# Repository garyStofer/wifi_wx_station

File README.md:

# wifi_wx_station
This project is for a full featured, self contained weather station that connects via WiFi to home network and uploads periodic readings
to various cloud based weather data ingestion service, such as Weather Underground, CWOP, WOW, etc.

The hardware is based on a Microchip controller with an attached Microchip WiFi module. 
The various sensors arepart of the project with the air data sensors (baro/temp/hyg) based onn i2C devices. 
The wind sensord are of unique solid state design ( optical, magnetic) and proide a high degree of precision, fidelity and reliability.

More information at http://wws.us.to

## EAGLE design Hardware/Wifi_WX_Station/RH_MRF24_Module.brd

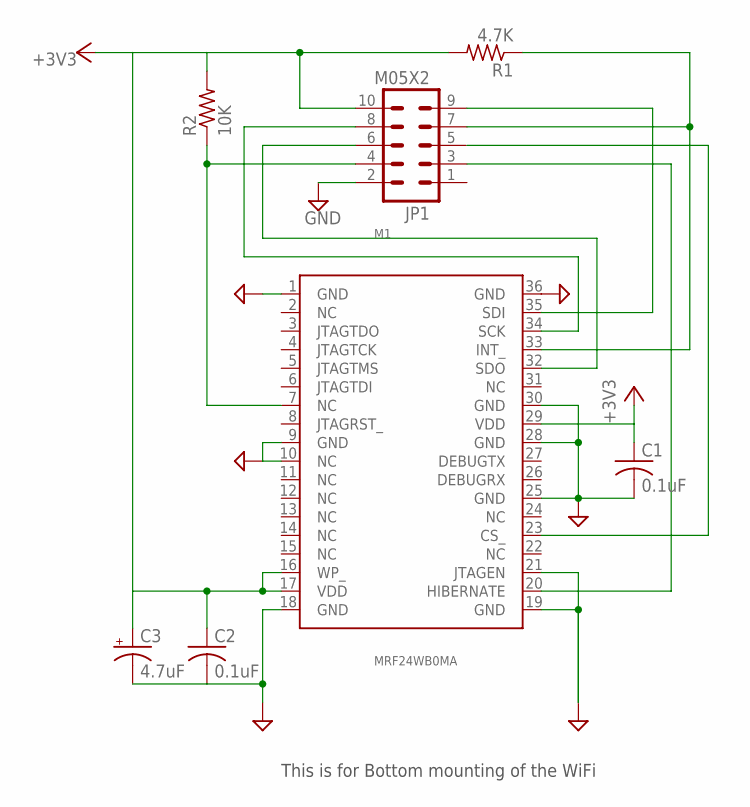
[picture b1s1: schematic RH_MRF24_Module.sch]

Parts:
C1, C2: 0.1uF; C0805
C3: 4.7uF; R/2012-12R
JP1: M05X2; 2X5-RA-HEADER
M1: MRF24WB0MA; MRF24W
R1: 4.7K; R0603
R2: 10K; R0603

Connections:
+3V3: C1.1, C2.1, C3.+, JP1.10, M1.16 (WP_), M1.17 (VDD), M1.29 (VDD), R1.2, R2.2
CS_: JP1.5, M1.23 (CS_)
GND: C1.2, C2.2, C3.-, JP1.2, M1.1 (GND), M1.9 (GND), M1.10 (NC), M1.18 (GND), M1.19 (GND), M1.21 (JTAGEN), M1.25 (GND), M1.28 (GND), M1.30 (GND), M1.36 (GND)
HIBER: JP1.3, M1.20 (HIBERNATE)
INT_: JP1.7, M1.33 (INT_), R1.1
RESET_: JP1.4, M1.7 (NC), R2.1
SCK: JP1.8, M1.34 (SCK)
SDI: JP1.9, M1.35 (SDI)
SDO: JP1.6, M1.32 (SDO)

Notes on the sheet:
This is for Bottom mounting of the WiFi

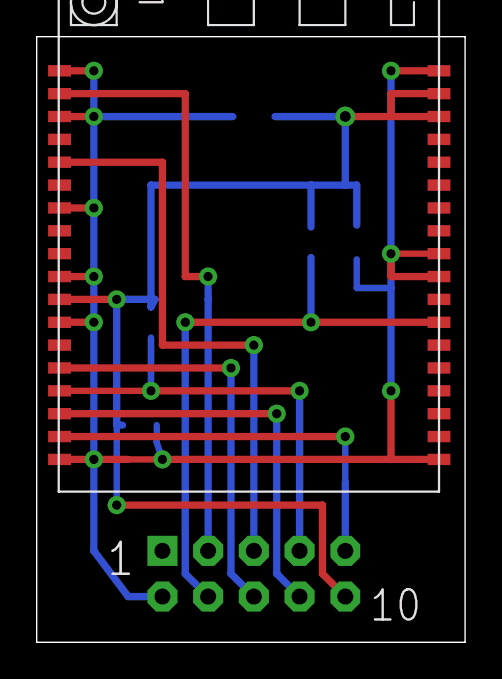
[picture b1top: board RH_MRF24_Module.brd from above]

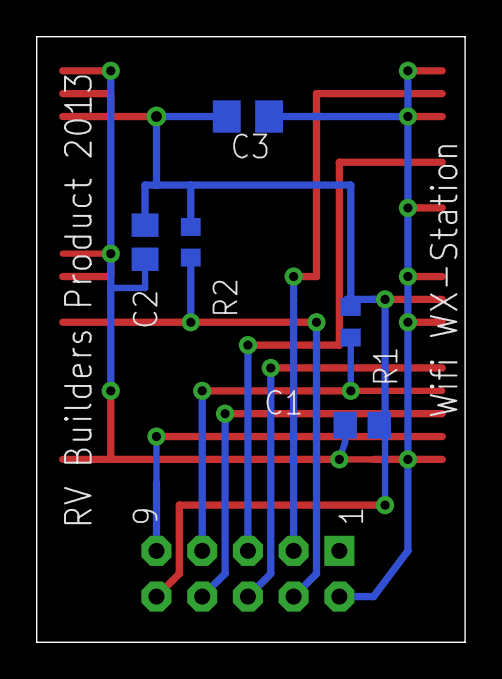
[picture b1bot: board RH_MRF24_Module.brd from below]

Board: 2 copper layers, 23.8 x 33.6 mm, 7 parts (6 on the bottom side), 9 nets.

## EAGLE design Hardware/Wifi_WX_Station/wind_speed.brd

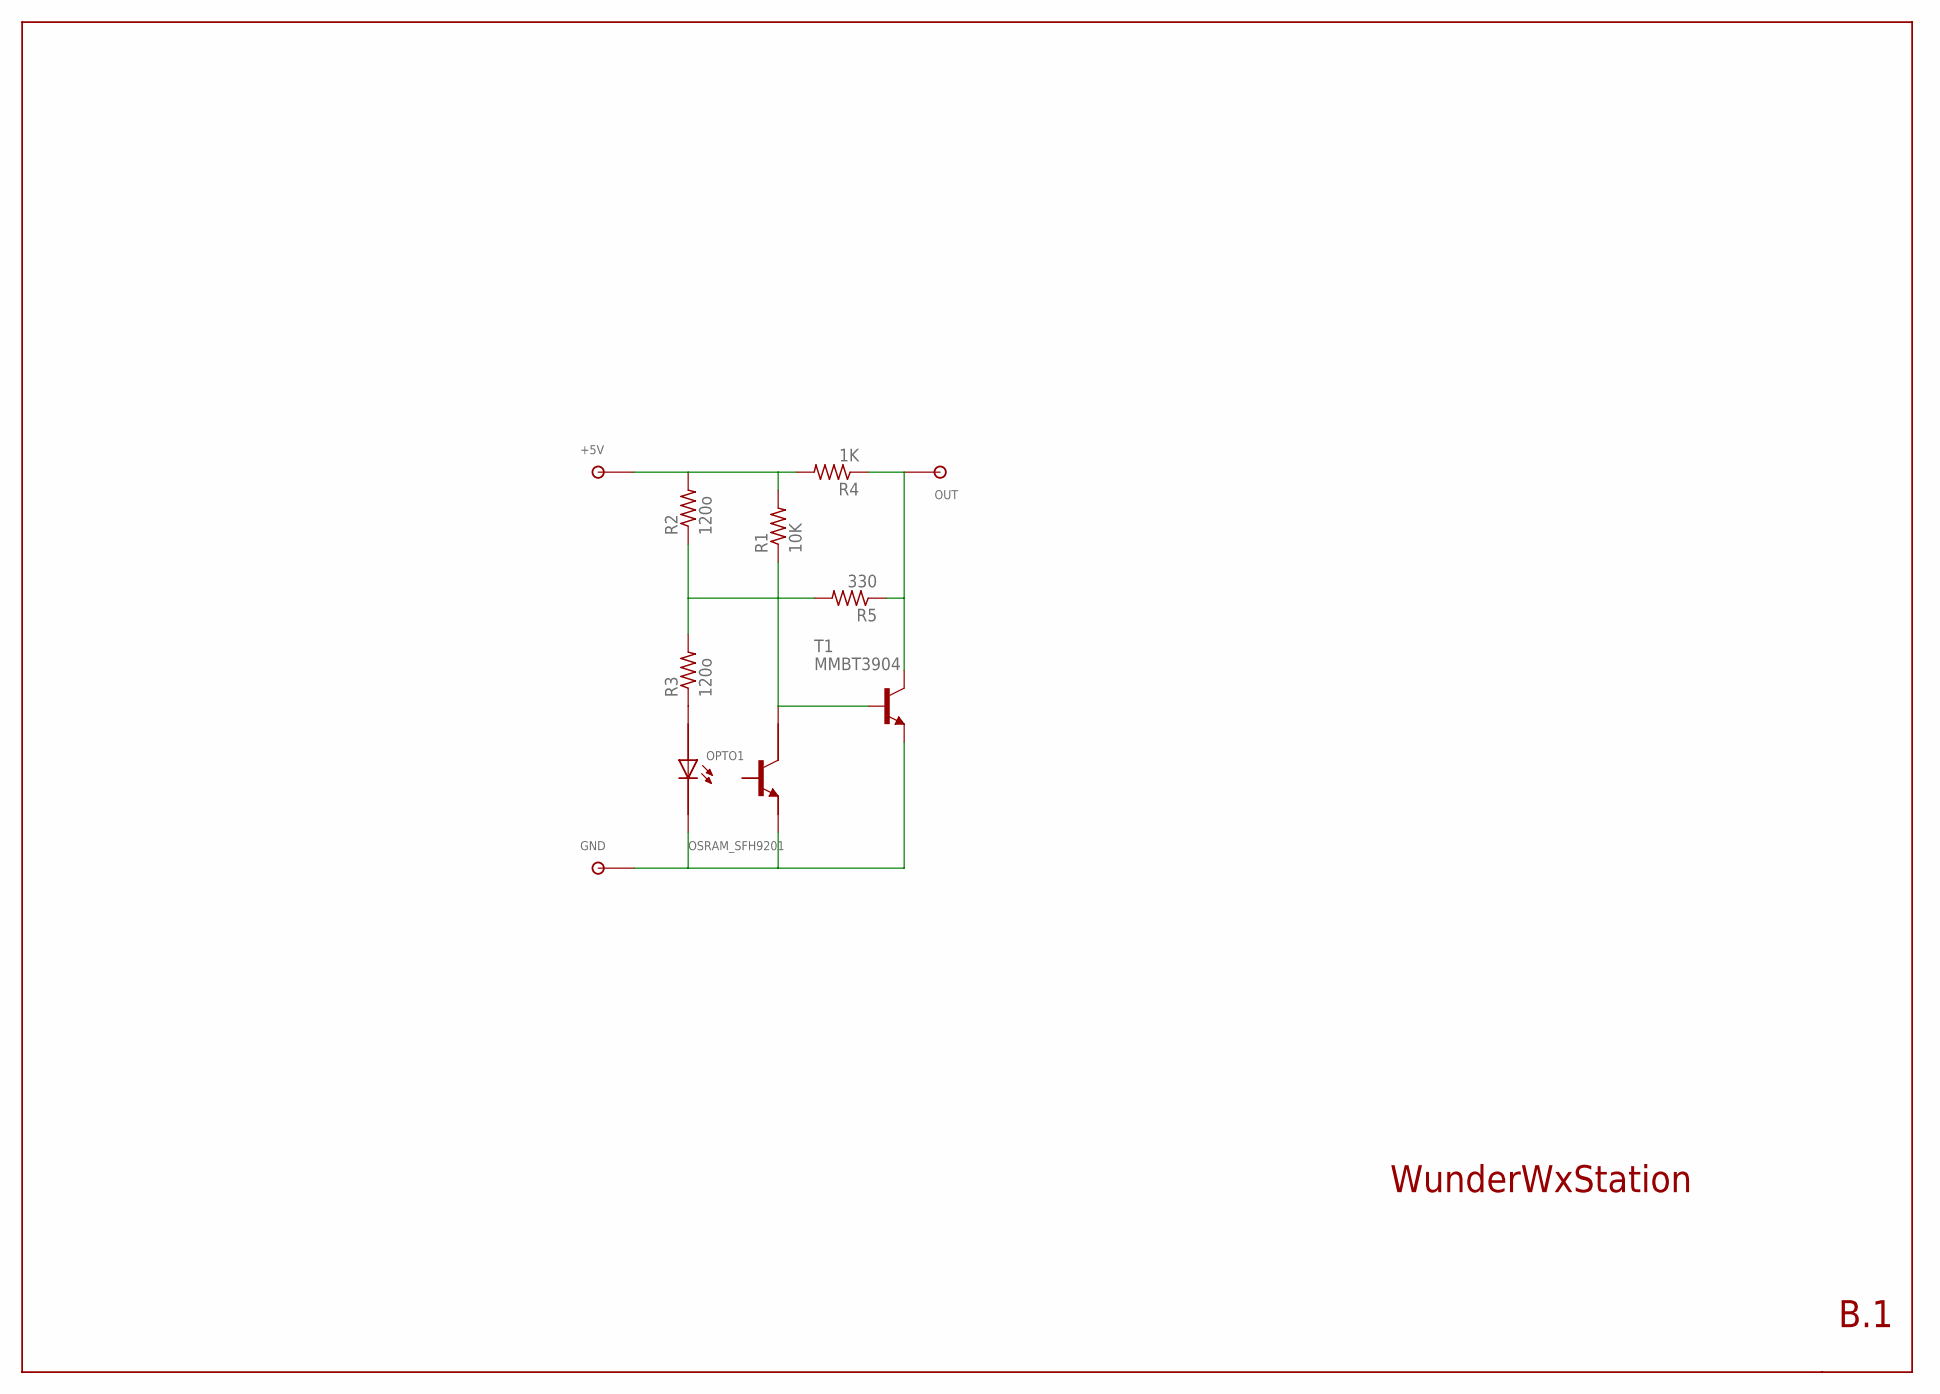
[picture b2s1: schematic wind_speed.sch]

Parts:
+5V: TPSOL; TP_SOL
GND: TPSOL; TP_SOL
OPTO1: OSRAM_SFH9201; OSRAM-6
OUT: TPSOL; TP_SOL
R1: 10K; R0603
R2, R3: 120o; R0603
R4: 1K; R0603
R5: 330; R0603
T1: MMBT3904; SOT23

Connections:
unnamed: OPTO1.P$4 (C), R1.1, T1.1 (B)
unnamed: GND.P$1, OPTO1.P$3 (E), OPTO1.P$6 (CATH), T1.2 (E)
unnamed: +5V.P$1, R1.2, R2.2, R4.2
unnamed: OUT.P$1, R4.1, R5.1, T1.3 (C)
unnamed: OPTO1.P$1 (AN), R3.1
unnamed: R2.1, R3.2, R5.2

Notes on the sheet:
WunderWxStation
B.1

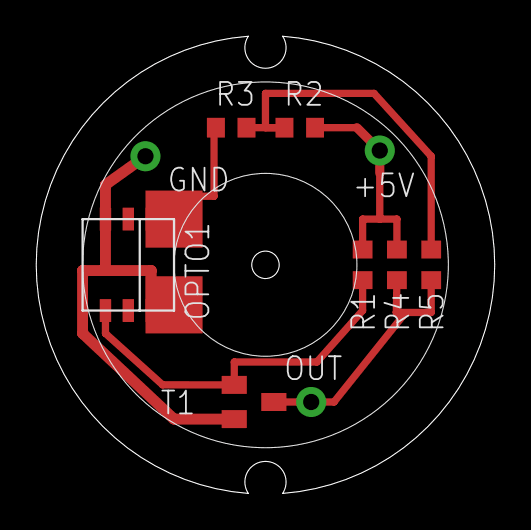
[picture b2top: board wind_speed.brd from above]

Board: 2 copper layers, 25.5 x 25.4 mm, 10 parts (0 on the bottom side), 6 nets.

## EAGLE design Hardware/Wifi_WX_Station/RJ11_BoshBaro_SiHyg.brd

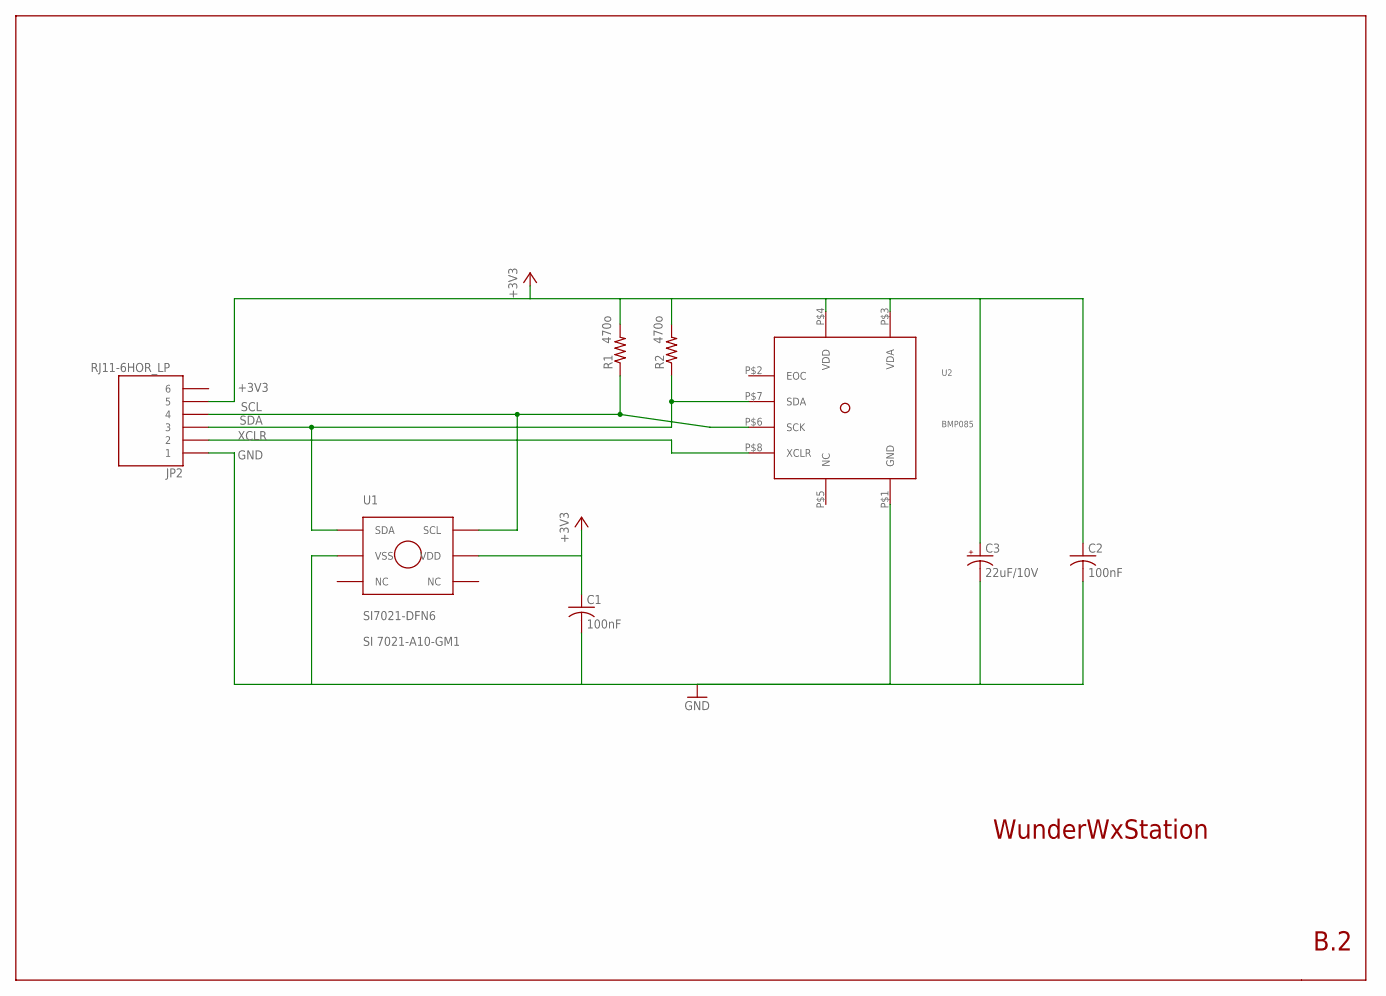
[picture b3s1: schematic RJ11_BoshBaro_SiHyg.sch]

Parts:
C1, C2: 100nF; C0805K
C3: 22uF/10V; SMC_B
JP2: RJ11-6HOR_LP; RJ11_HOR_LP
R1, R2: 470o; R0603
U1: SI7021-DFN6; DFN-6_SILABS
U2: BMP085; LCC8

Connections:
+3V3: C1.1, C2.1, C3.+, JP2.P$5 (5), R1.2, R2.2, U1.P$5 (VDD), U2.P$3 (VDA), U2.P$4 (VDD)
GND: C1.2, C2.2, C3.-, JP2.P$1 (1), U1.P$2 (VSS), U2.P$1 (GND)
SCL: JP2.P$4 (4), R1.1, U1.P$6 (SCL), U2.P$6 (SCK)
SDA: JP2.P$3 (3), R2.1, U1.P$1 (SDA), U2.P$7 (SDA)
XCLR: JP2.P$2 (2), U2.P$8 (XCLR)

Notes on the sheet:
WunderWxStation
B.2
SI 7021-A10-GM1

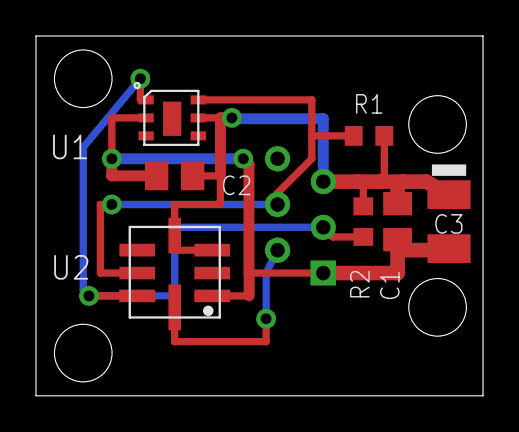
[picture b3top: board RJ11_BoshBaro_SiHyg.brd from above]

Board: 2 copper layers, 24.8 x 20.0 mm, 8 parts (1 on the bottom side), 5 nets.

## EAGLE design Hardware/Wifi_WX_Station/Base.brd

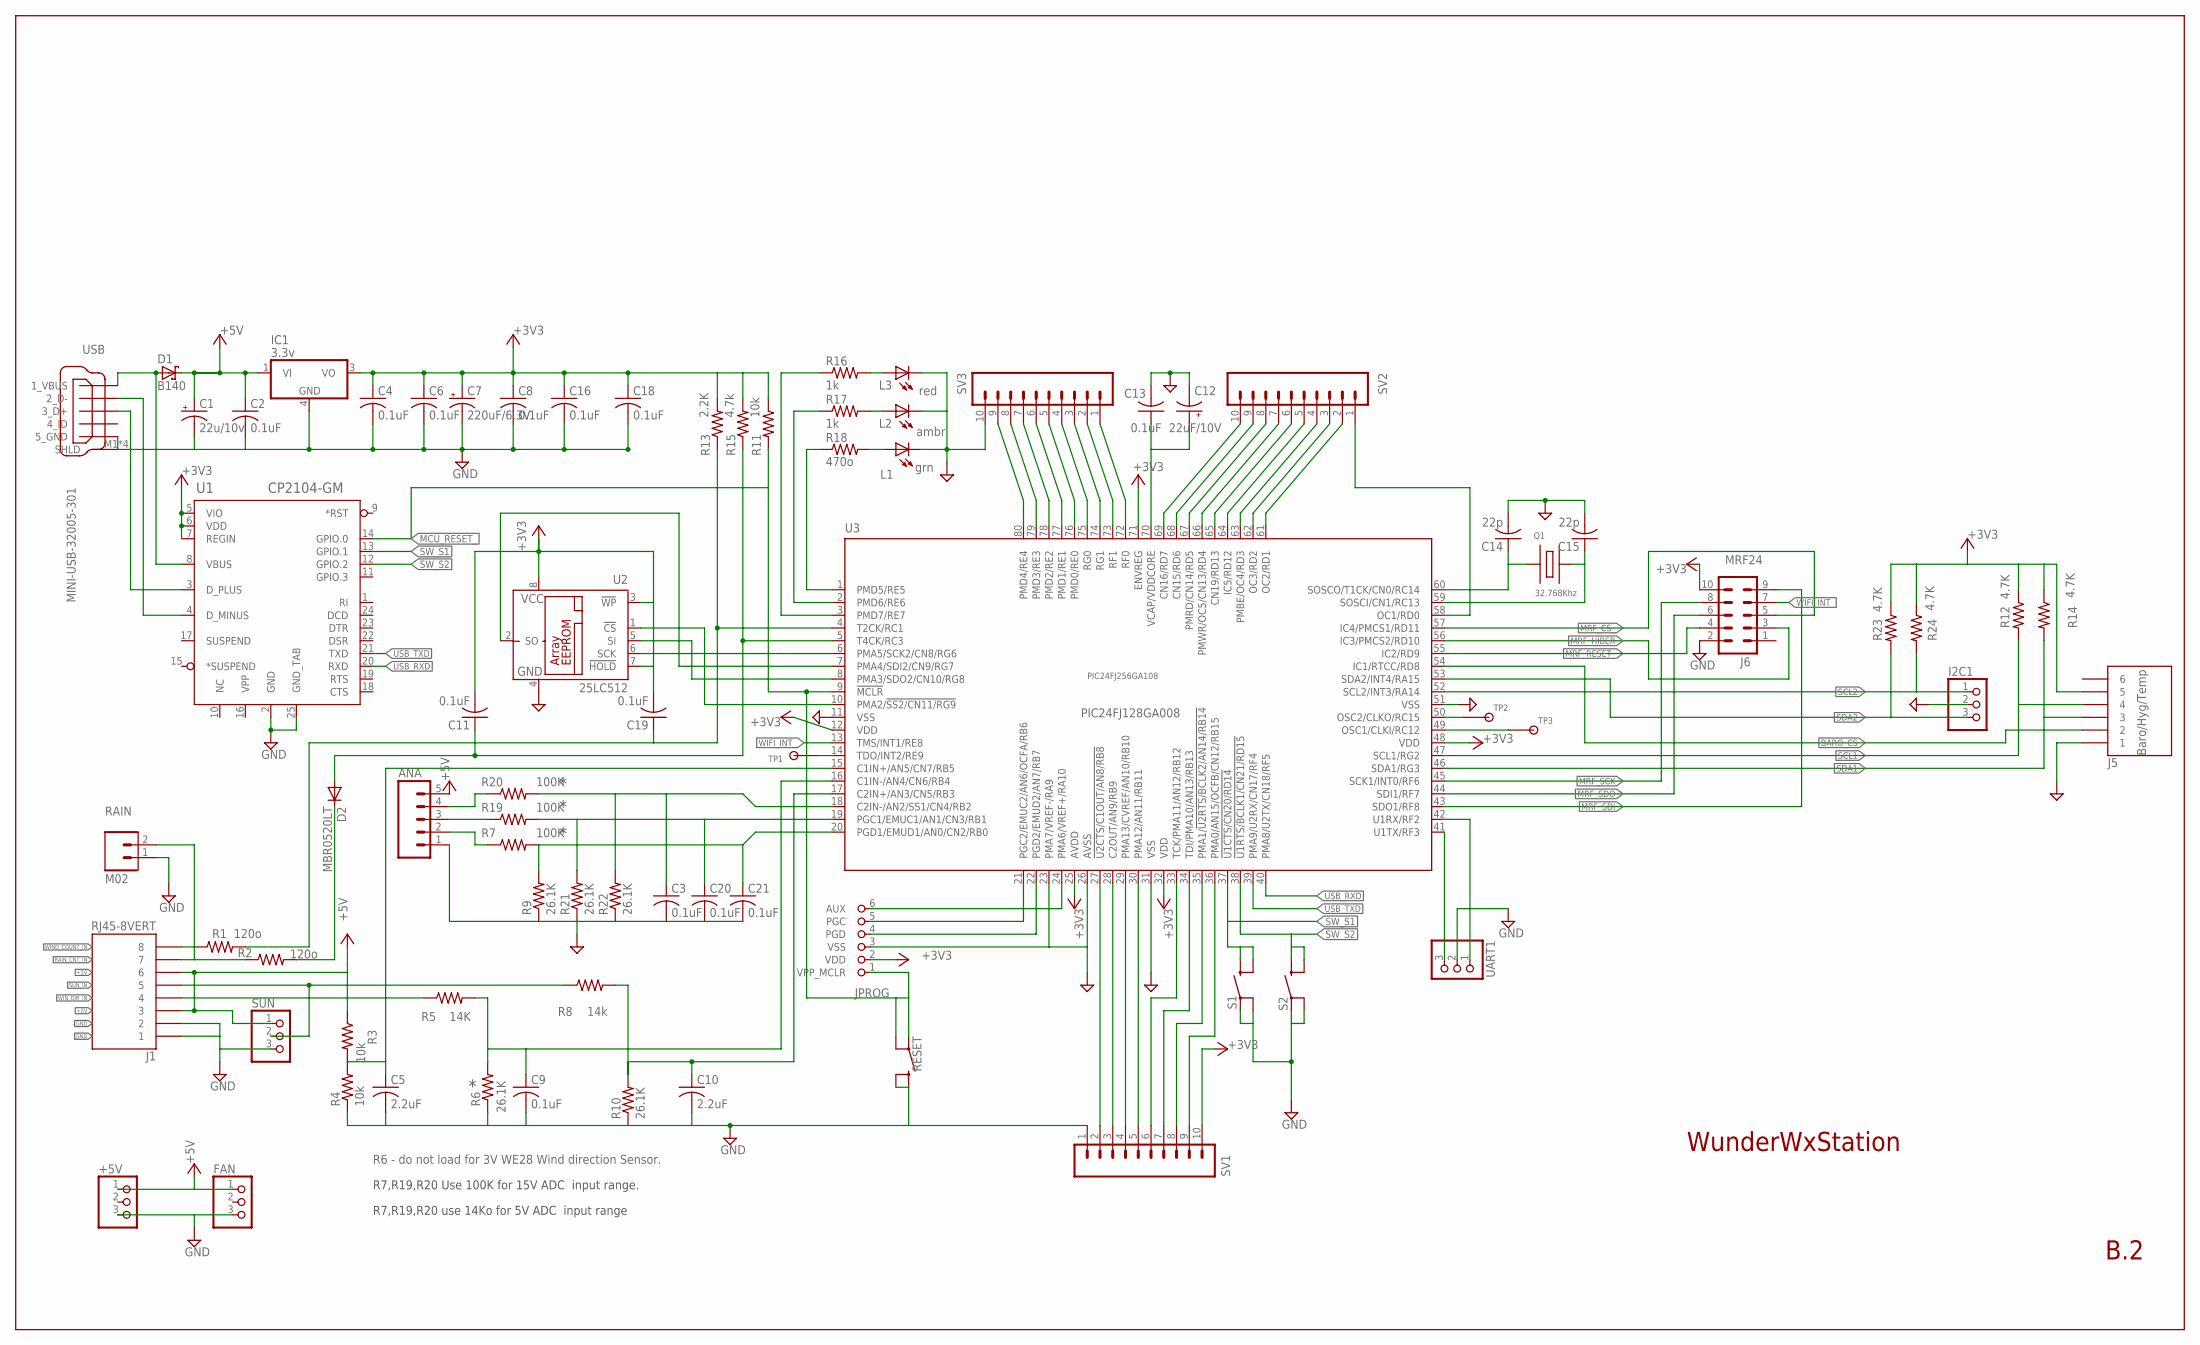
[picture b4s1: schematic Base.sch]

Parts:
+5V: PINHD-1X3MOLEX_KK; 1X3_MOLEX_KK
ANA: M05PTH; 1X05
C1: 22u/10v; SMC_B
C2, C3, C4, C6, C8, C9, C11, C13, C16, C18, C19, C20, C21: 0.1uF; C0805
C5, C10: 2.2uF; C0805
C7: 220uF/6.3V; SMC_D
C12: 22uF/10V; SMC_B
C14, C15: 22p; C0603
D1: B140; SMB
D2: MBR0520LT; SOD123
FAN: PINHD-1X3MOLEX_KK; 1X3_MOLEX_KK
I2C1: PINHD-1X3; 1X03
IC1: 3.3v; DPACK
J1: RJ45-8VERT; RJ45_VERT
J5: RJ11-6VERT_LP; RJ11-6-VERT
J6: M05X22X5FE; 2X5FEMALE
JPROG: PIKIT2_PRG; 1X06_PIKIT
L1: grn; CHIP-LED0603
L2: ambr; CHIP-LED0603
L3: red; CHIP-LED0603
Q1: 32.768Khz; CRYSTAL32_SMT
R1, R2: 120o; R0603
R3, R4, R11: 10k; R0603
R5: 14K; R0603
R6, R9, R10, R21, R22: 26.1K; R0603
R7, R19, R20: 100K; R0603
R8: 14k; R0603
R12, R14, R23, R24: 4.7K; R0603
R13: 2.2K; R0603
R15: 4.7k; R0603
R16, R17: 1k; R0603
R18: 470o; R0603
RAIN: M02; 1X02
RESET: SWITCH-MOMENTARY-2SMD; TACTILE_SWITCH_SMD
S1, S2: SWITCH-MOMENTARY-2SMD; TACTILE_SWITCH_SMD
SUN: PINHD-1X3MOLEX_KK; 1X3_MOLEX_KK
SV1, SV2, SV3: M10"; 1X10
TP1: TP10R
TP2, TP3: TP6R; TP06R
U1: CP2104-GM; QFN24_4X4
U2: 25LC512; SO-08
U3: PIC24FJ128GA008; TQFP80-12X12
UART1: PINHD-1X3; 1X03
USB: MINI-USB-32005-301; 32005-301

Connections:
+3V3: C4.1, C6.1, C7.+, C8.1, C11.2, C16.1, C18.1, C19.2, IC1.3 (VO), J5.P$5 (5), J6.10, JPROG.2 (VDD), R11.1, R12.1, R13.2, R14.1, R15.2, R23.1, R24.1, SV1.10, U1.5 (VIO), U1.6 (VDD), U1.7 (REGIN), U2.3 (!WP), U2.7 (!HOLD), U2.8 (VCC), U3.12 (VDD), U3.25 (AVDD), U3.32 (VDD), U3.48 (VDD), U3.71 (ENVREG)
+5V: +5V.1, ANA.5, C1.+, C2.1, D1.C, FAN.1, IC1.1 (VI), J1.P$3 (3), J1.P$6 (6), R3.1, SUN.1
BARO_CS: J5.P$2 (2), U3.54 (IC1/RTCC/RD8)
GND: +5V.3, ANA.1, C1.-, C2.2, C3.2, C4.2, C5.2, C6.2, C7.-, C8.2, C9.2, C10.2, C12.-, C13.2, C14.2, C15.2, C16.2, C18.2, C20.2, C21.2, FAN.3, I2C1.2, IC1.4 (GND), J1.P$1 (1), J1.P$2 (2), J5.P$1 (1), J6.2, JPROG.3 (VSS), L1.C, L2.C, L3.C, R4.1, R6.1, R9.1, R10.1, R21.1, R22.1, RAIN.1, RESET.3 (2), RESET.4 (3), S1.1, S1.2 (4), S2.1, S2.2 (4), SUN.3, SV1.1, SV3.10, U1.2 (GND), U1.25 (GND_TAB), U2.4 (GND), U3.11 (VSS), U3.23 (PMA7/VREF-/RA9), U3.26 (AVSS), U3.31 (VSS), U3.51 (VSS), UART1.2, USB.5_USB_GND (5_GND), USB.M1 (SHLD), USB.M2 (SHLD), USB.M3 (SHLD), USB.M4 (SHLD)
MCU_RESET_: JPROG.1 (VPP_MCLR), R11.2, RESET.1, RESET.2 (4), U1.14 (GPIO.0), U3.9 (!MCLR)
MRF_CS_: J6.5, U3.57 (IC4/PMCS1/RD11)
MRF_HIBER: J6.3, U3.56 (IC3/PMCS2/RD10)
MRF_RESET_: J6.4, U3.55 (IC2/RD9)
MRF_SCK: J6.8, U3.45 (SCK1/INT0/RF6)
MRF_SDI: J6.9, U3.43 (SDO1/RF8)
MRF_SDO: J6.6, U3.44 (SDI1/RF7)
unnamed: D2.C, R2.2
unnamed: C15.1, Q1.P$3, U3.59 (SOSCI/CN1/RC13)
unnamed: TP2.TP_1, U3.50 (OSC2/CLKO/RC15)
unnamed: R18.1, U3.1 (PMD5/RE5)
unnamed: C14.1, Q1.P$2, U3.60 (SOSCO/T1CK/CN0/RC14)
unnamed: TP1.TP_1, U3.14 (TDO/INT2/RE9)
unnamed: D1.A, U1.8 (VBUS), USB.1_VBUS
unnamed: SV2.2, U3.61 (OC2/RD1)
unnamed: SV2.3, U3.62 (OC3/RD2)
unnamed: SV2.4, U3.63 (PMBE/OC4/RD3)
unnamed: SV2.5, U3.64 (IC5/RD12)
unnamed: TP3.TP_1, U3.49 (OSC1/CLKI/RC12)
unnamed: SV2.6, U3.65 (CN19/RD13)
unnamed: JPROG.5 (PGC), U3.21 (PGC2/EMUC2/AN6/OCFA/RB6)
unnamed: JPROG.4 (PGD), U3.22 (PGD2/EMUD2/AN7/RB7)
unnamed: L3.A, R16.2
unnamed: C12.+, C13.1, U3.70 (VCAP/VDDCORE)
unnamed: L2.A, R17.2
unnamed: L1.A, R18.2
unnamed: C21.1, R7.2, R9.2, U3.20 (PGD1/EMUD1/AN0/CN2/RB0)
unnamed: ANA.4, R20.1
unnamed: C20.1, R19.2, R21.2, U3.19 (PGC1/EMUC1/AN1/CN3/RB1)
unnamed: U2.2 (SO), U3.7 (PMA4/SDI2/CN9/RG7)
unnamed: SV2.7, U3.66 (PMWR/OC5/CN13/RD4)
unnamed: U2.1 (!CS), U3.10 (PMA2/!SS2/CN11/RG9)
unnamed: C3.1, R20.2, R22.2, U3.18 (C2IN-/AN2/SS1/CN4/RB2)
unnamed: U2.6 (SCK), U3.6 (PMA5/SCK2/CN8/RG6)
unnamed: ANA.3, R19.1
unnamed: ANA.2, R7.1
unnamed: U2.5 (SI), U3.8 (PMA3/SDO2/CN10/RG8)
unnamed: R17.1, U3.2 (PMD6/RE6)
unnamed: R16.1, U3.3 (PMD7/RE7)
unnamed: SV2.8, U3.67 (PMRD/CN14/RD5)
unnamed: SV2.9, U3.68 (CN15/RD6)
unnamed: SV2.10, U3.69 (CN16/RD7)
unnamed: SV3.1, U3.72 (RF0)
unnamed: SV2.1, U3.58 (OC1/RD0)
unnamed: U3.41 (U1TX/RF3), UART1.3
unnamed: U3.42 (U1RX/RF2), UART1.1
unnamed: SV1.2, U3.27 (!U2CTS/C1OUT/AN8/RB8)
unnamed: SV1.3, U3.28 (C2OUT/AN9/RB9)
unnamed: SV1.4, U3.29 (PMA13/CVREF/AN10/RB10)
unnamed: SV1.5, U3.30 (PMA12/AN11/RB11)
unnamed: SV1.6, U3.33 (TCK/PMA11/AN12/RB12)
unnamed: SV1.7, U3.34 (TDI/PMA10/AN13/RB13)
unnamed: SV1.8, U3.35 (PMA1/!U2RTS/BCLK2/AN14/RB14)
unnamed: SV1.9, U3.36 (PMA0/AN15/OCFB/CN12/RB15)
unnamed: SV3.2, U3.73 (RF1)
unnamed: SV3.3, U3.74 (RG1)
unnamed: SV3.4, U3.75 (RG0)
unnamed: SV3.5, U3.76 (PMD0/RE0)
unnamed: SV3.6, U3.77 (PMD1/RE1)
unnamed: SV3.7, U3.78 (PMD2/RE2)
unnamed: SV3.8, U3.79 (PMD3/RE3)
unnamed: SV3.9, U3.80 (PMD4/RE4)
unnamed: JPROG.6 (AUX), U3.24 (PMA6/VREF+/RA10)
unnamed: C5.1, R3.2, R4.2, U3.15 (C1IN+/AN5/CN7/RB5)
RAIN_CNT_IN: J1.P$7 (7), R2.1, RAIN.2
RAIN_COUNT: C11.1, D2.A, R15.1, U3.5 (T4CK/RC3)
SCL1: J5.P$4 (4), R12.2, U3.47 (SCL1/RG2)
SCL2: I2C1.1, R24.2, U3.52 (SCL2/INT3/RA14)
SDA1: J5.P$3 (3), R14.2, U3.46 (SDA1/RG3)
SDA2: I2C1.3, R23.2, U3.53 (SDA2/INT4/RA15)
SUN_ADC_IN: C10.1, R8.2, R10.2, U3.17 (C2IN+/AN3/CN5/RB3)
SUN_IN: J1.P$5 (5), R8.1, SUN.2
SW_S1: S1.3 (2), S1.4 (3), U1.13 (GPIO.1), U3.37 (!U1CTS/CN20/RD14)
SW_S2: S2.3 (2), S2.4 (3), U1.12 (GPIO.2), U3.38 (!U1RTS/BCLK1/CN21/RD15)
USB_D+: U1.3 (D_PLUS), USB.3_D+
USB_D-: U1.4 (D_MINUS), USB.2_D-
USB_RXD: U1.20 (RXD), U3.40 (PMA8/U2TX/CN18/RF5)
USB_TXD: U1.21 (TXD), U3.39 (PMA9/U2RX/CN17/RF4)
WIFI_INT_: J6.7, U3.13 (TMS/INT1/RE8)
WIND_ADC_IN: C9.1, R5.2, R6.2, U3.16 (C1IN-/AN4/CN6/RB4)
WIND_COUNT: C19.1, R1.2, R13.1, U3.4 (T2CK/RC1)
WIND_COUNT_IN: J1.P$8 (8), R1.1
WIN_DIR_IN: J1.P$4 (4), R5.1

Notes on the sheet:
Baro/Hyg/Temp
PIC24FJ256GA108
MRF24
R6 - do not load for 3V WE28 Wind direction Sensor.
B.2
WunderWxStation
R7,R19,R20 Use 100K for 15V ADC input range.
R7,R19,R20 use 14Ko for 5V ADC input range

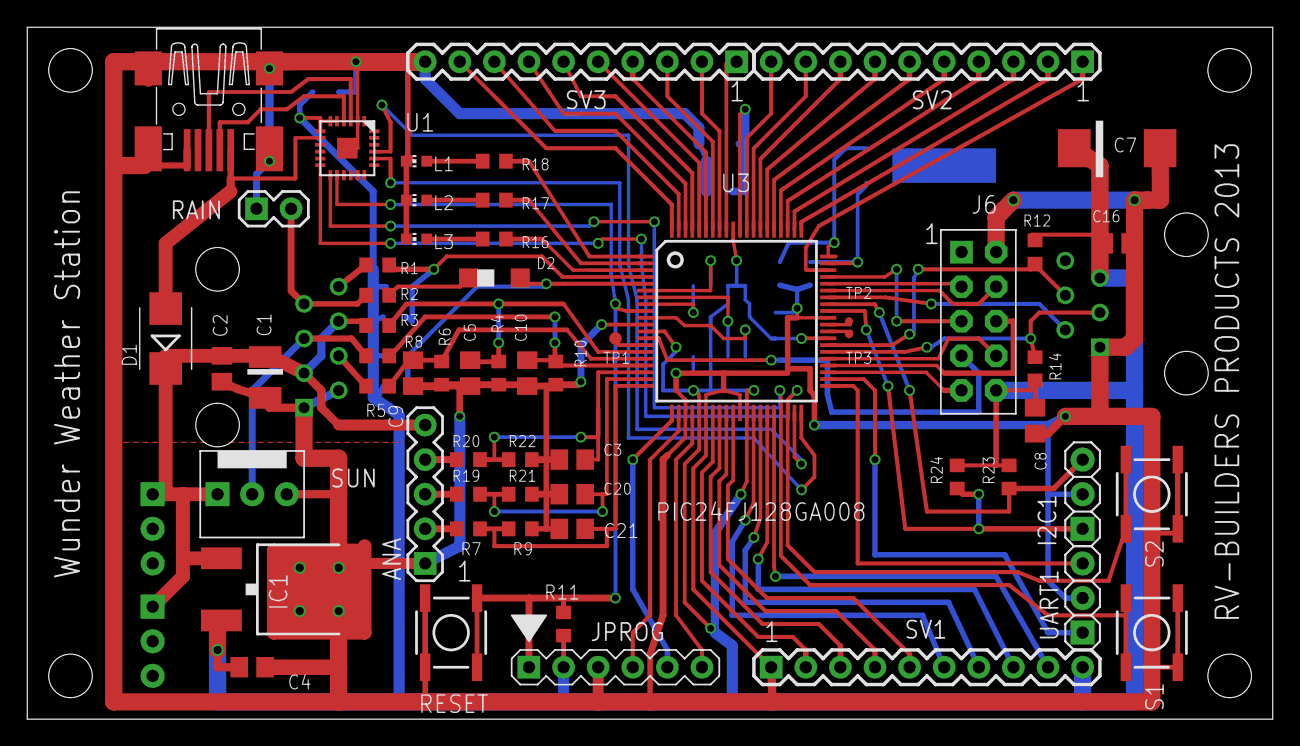
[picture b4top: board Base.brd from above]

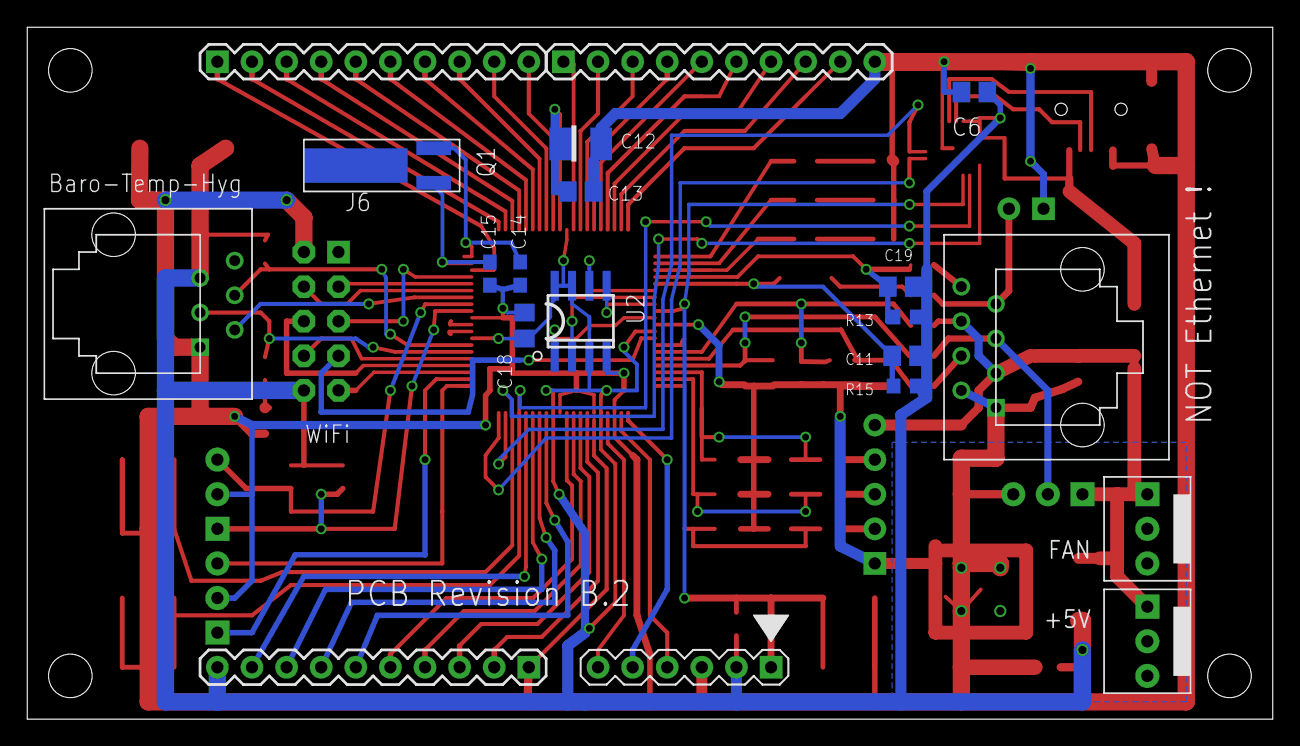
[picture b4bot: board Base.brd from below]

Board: 2 copper layers, 91.4 x 50.8 mm, 75 parts (20 on the bottom side), 87 nets.

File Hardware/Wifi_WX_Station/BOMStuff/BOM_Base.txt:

Partlist

Exported from Base.brd at 3/5/2013 4:10:53 PM

EAGLE Version 6.3.0 Copyright (c) 1988-2012 CadSoft

Assembly variant: 

Part     Value                 Package            Library   Position (inch)       Orientation

ANA                            1X04               wifi_WX   (1.15 0.5)            R90
C1       22u/10v               SMC_B              rcl       (0.6875 0.9875)       R270
C2       0.1uF                 C0805              rcl       (0.5625 1.0125)       R270
C3       0.1uF                 C0805              rcl       (1.55 0.85)           R180
C4       0.1uF                 C0805              rcl       (0.65 0.15)           R0
C5       0.1uF                 C0805              rcl       (1.28 1)              R270
C6       0.1uF                 C0805              rcl       (0.8625 1.8125)       MR180
C7       330uF/6V              SMC_D              rcl       (3.1 1.65)            R180
C8       0.1uF                 C0805              rcl       (3.075 0.9)           R270
C9       2.2uF                 C0805              rcl       (1.115 1)             R270
C10      2.2uF                 C0805              rcl       (1.445 1)             R270
C11      0.1uF                 C0805              rcl       (1.0625 1.05)         MR0
C12      22uF/10V              SMC_B              rcl       (2 1.6625)            MR0
C13      0.1uF                 C0805              rcl       (2 1.525)             MR0
C14      22p                   C0603              rcl       (2.175 1.2875)        MR270
C15      22p                   C0603              rcl       (2.2625 1.2875)       MR270
C16      0.1uF                 C0805              rcl       (3.1 1.5)             R180
C18      0.1uF                 C0805              rcl       (2.1625 1.1375)       MR90
C19      0.1uF                 C0805              rcl       (1.075 1.25)          MR0
C20      0.1uF                 C0805              rcl       (1.55 0.7)            R180
C21      0.1uF                 C0805              rcl       (1.55 0.55)           R180
D1       B140                  SMB                diode     (0.4 1.1)             R90
FAN                            1X3_MOLEX_KK       wifi_WX   (0.475 0.5375)        MR270
I2C1                           1X03               wifi_WX   (2.85 0.5)            R0
IC1      3.3v                  DPACK              wifi_WX   (0.75 0.375)          R270
J1       RJ45-8VERT            RJ45_VERT          wifi_WX   (0.55 0.85)           MR90
J5                             1X5_MOLEX_KK       wifi_WX   (3.125 0.9)           MR90
J6       M05X22X5FE            2X5FEMALE          wifi_WX   (2.75 1.15)           R0
JPROG                          1X06_PIKIT         wifi_WX   (1.75 0.15)           MR180
L1       grn                   CHIP-LED0603       led       (1.125 1.6125)        R90
L2       ambr                  CHIP-LED0603       led       (1.125 1.5)           R90
L3       red                   CHIP-LED0603       led       (1.125 1.3875)        R90
Q1       32.768khz             CRYSTAL32_SMT      wifi_WX   (2.55 1.625)          MR0
R1       120o                  R0603              rcl       (1.0125 1.3125)       R0
R2       120o                  R0603              rcl       (1.0125 1.225)        R0
R3       10k                   R0603              rcl       (1.0125 1.1375)       R0
R4       10k                   R0603              rcl       (1.3625 1)            R90
R5       8.2k                  R0603              rcl       (1.0125 0.9625)       R0
R6       26.1k                 R0603              rcl       (1.1975 1)            R90
R7       14k                   R0603              rcl       (1.275 0.55)          R0
R8       14k                   R0603              rcl       (1.0125 1.05)         R0
R9       26.1K                 R0603              rcl       (1.4 0.55)            R180
R10      26.1K                 R0603              rcl       (1.5275 1)            R90
R11      10k                   R0603              rcl       (1.6 0.275)           R90
R12      4.7K                  R0603              rcl       (2.9875 1.3125)       R270
R13      4.7k                  R0603              rcl       (1.0625 1.1625)       MR0
R14      4.7K                  R0603              rcl       (2.9875 1.025)        R90
R15      4.7k                  R0603              rcl       (1.0625 0.9625)       MR0
R16      1k                    R0603              rcl       (1.35 1.3875)         R180
R17      1k                    R0603              rcl       (1.35 1.5)            R180
R18      470o                  R0603              rcl       (1.35 1.6125)         R180
R19      14k                   R0603              rcl       (1.275 0.7)           R0
R20      14k                   R0603              rcl       (1.275 0.85)          R0
R21      26.1K                 R0603              rcl       (1.4 0.7)             R180
R22      26.1K                 R0603              rcl       (1.4 0.85)            R180
R23      4.7K                  R0603              rcl       (2.8875 0.75)         R270
R24      4.7K                  R0603              rcl       (2.7375 0.75)         R270
RESET    SWITCH-MOMENTARY-2SMD TACTILE_SWITCH_SMD wifi_WX   (1.225 0.25)          R270
S1       SWITCH-MOMENTARY-2SMD TACTILE_SWITCH_SMD wifi_WX   (3.25 0.3)            R270
S2       SWITCH-MOMENTARY-2SMD TACTILE_SWITCH_SMD wifi_WX   (3.25 0.65)           R270
SUN                            1X3_MOLEX_KK       wifi_WX   (0.5 0.525)           R0
SV1      M10"                  1X10               wifi_WX   (2.15 0.15)           MR180
SV2      M10"                  1X10               wifi_WX   (3.05 1.9)            MR0
SV3      M10"                  1X10               wifi_WX   (2.05 1.9)            MR0
TP1      TP                    TP06R              wifi_WX   (1.7 1.1)             R0
TP2      TP                    TP06R              wifi_WX   (2.375 1.15)          R0
TP3      TP                    TP06R              wifi_WX   (2.375 1.1125)        R0
U1       CP2104-GM             QFN24_4X4          wifi_WX   (0.925 1.65)          R270
U2       25LC512               SO-08              microchip (2 1.15)              MR0
U3       PIC24FJ128GA008       TQFP80-12X12       wifi_WX   (2.05 1.15)           R0
UART1                          1X03               wifi_WX   (2.45 0.5)            R180
USB      MINI-USB-32005-301    32005-301          wifi_WX   (0.525 1.7625)        R270

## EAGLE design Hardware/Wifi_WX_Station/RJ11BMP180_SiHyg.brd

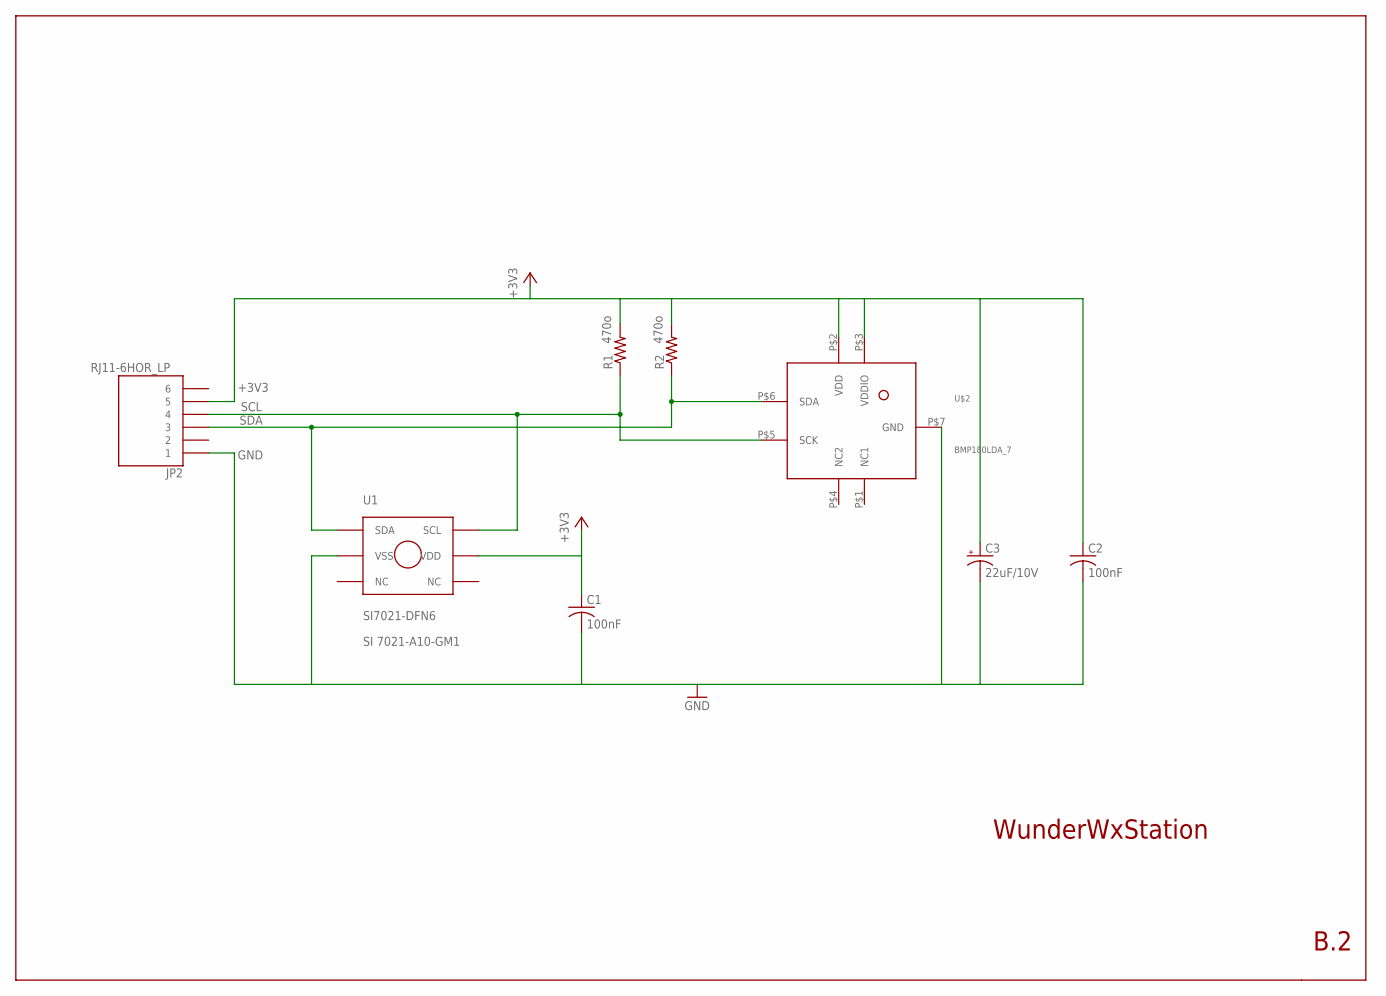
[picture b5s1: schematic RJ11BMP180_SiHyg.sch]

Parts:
C1, C2: 100nF; C0805K
C3: 22uF/10V; SMC_B
JP2: RJ11-6HOR_LP; RJ11_HOR_LP
R1, R2: 470o; R0603
U1: SI7021-DFN6; DFN-6_SILABS
U$2: BMP180LDA_7; LGA_7

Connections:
+3V3: C1.1, C2.1, C3.+, JP2.P$5 (5), R1.2, R2.2, U1.P$5 (VDD), U$2.P$2 (VDD), U$2.P$3 (VDDIO)
GND: C1.2, C2.2, C3.-, JP2.P$1 (1), U1.P$2 (VSS), U$2.P$7 (GND)
SCL: JP2.P$4 (4), R1.1, U1.P$6 (SCL), U$2.P$5 (SCK)
SDA: JP2.P$3 (3), R2.1, U1.P$1 (SDA), U$2.P$6 (SDA)

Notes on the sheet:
WunderWxStation
B.2
SI 7021-A10-GM1

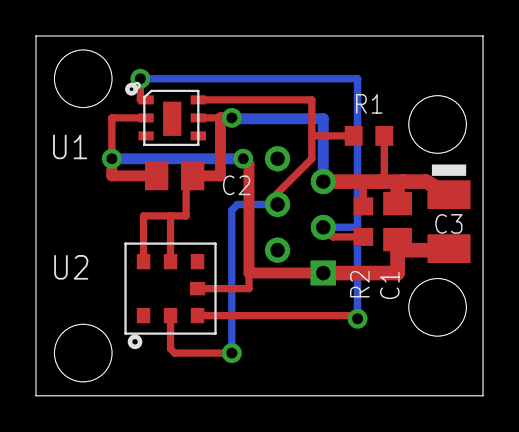
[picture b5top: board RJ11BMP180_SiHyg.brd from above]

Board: 2 copper layers, 24.8 x 20.0 mm, 8 parts (1 on the bottom side), 4 nets.

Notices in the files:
Firmware/Rel_B_1/PIC_WIFI_WX_STATION/Wifi_Wunder_Station.X/src/Configs/HWP EX16_MRF24W XC16.h:
Copyright (C) 2002-2010 Microchip Technology Inc.  All rights
